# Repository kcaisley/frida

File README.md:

# FRIDA: Fast radiation imaging digitizer array

Frame-based radiation detectors with integrating front-ends are especially well-suited for applications like electron microscopy and X-ray imaging where hit-rates are high, spatial resolution should be maximized with simple pixels, and energy resolution is needed, but particles need not be individually discriminated in time, space, or spectrum. In an experimental setting, fast frame rates allow for real time in-situ observations. Potential subjects include rapid chemical processes, molecular dynamics of proteins, crystal nucleation and growth, material phase transitions, thermal conductivity, charge transfer, and mechanical strain.

This project pursues the possibility of a single-reticle array larger than 1 Mpixel with a continuous frame-rate surpassing 100,000 fps. For the conjunction of these two specifications to be met, one must have a compact and power efficient bank of column-parallel data converters, which at 10-12 bit resolution churn out data at a rate in excess of 1000 Gbps. To fit within the constraints of a chip bottom, the converter fabric must respect a restricted metric of 1 W/cm^2 while exceeding a 5 ksps/µm^2 sampling rate density. Successive-approximation ADCs are identified as the optimal choice, and various topologies and techniques will be analyzed to meet our goals.

Research question: How do we best allocate the quantity and weighting of SA bit positions, in order to yeild the highest resolution (in ENOB) for a given power, area, and power budget, and with a given amount of power supply noise?

## Block diagram of example system

## Modeling and analysis workflow

## Past designs vs current target

| Design                  | EDET DCD    | CoRDIA     | pre-Helena | Helena      |
|-------------------------|-------------|------------|------------|-------------|
| ADC resolution          | 8-bit       | 10-bit     | 8-bit      | 10-bit      |
| Conversion rate         | 10 MHz      | 2.5MHz     | 5 MHz      | 10 MHz      |
| Area of one ADC         | 100x200 μm² | 80x330 μm² | 60x800 μm² | 20x100 μm²  |
| Power of one ADC        | 1800 μW     | 30 μW      | 700 μW     | 100 μW      |
| FOM_csa (conv/sec/area) | 500 Hz/μm²  | 95 Hz/μm²  | 105 Hz/μm² | 5000 Hz/μm² |
| FOM_epc (energy/conv)   | 180 pJ      | 12 pJ      | 155 pJ     | 10 pJ       |
| FOM_ppa (power/area)    | 9.0 W/cm²   | 0.11 W/cm² | 1.45 W/cm² | 5.0 W/cm²   |
| ADC qty Mpix @ 100 KHz  | 10000       | 40000      | 20000      | 10000       |
| ADCs total pixel rate   | 100 Gpx/s   | 100 Gpx/s  | 100 Gpx/s  | 100 Gpx/s   |
| ADCs total data rate    | 800 Gb/s    | 1 Tb/s     | 800 Gb/s   | 1 Tb/s      |
| ADCs total area         | 2.0 cm²     | 10.5 cm²   | 9.6 cm²    | 0.2 cm²     |
| ADCs total power        | 35.0 W      | 1.2 W      | 14 W       | 1.0 W       |

NOTE: EDET DCD 1800 μW seems high, does it erroneously includes input amp?

# Project organization (proposal)

```
├── src
├── hdl
├── oa  (Caeleste input collateral eventually to be deleted)
├── netlists (library of generic netlists, and Verilog A models -> converted with find+replace)
├── impl
│   └── tsmc65 (1. impl netlists/oa schems/layouts/ 2. pointers to )
│   └── tsmc28
├── sim
│   └── tsmc65 (runs against impl netlists, since we have to have to include external libs)
│   └── tsmc28
├── tech
│   └── tsmc65 (EDA env start dir)
│   └── tsmc28
├── writing
```

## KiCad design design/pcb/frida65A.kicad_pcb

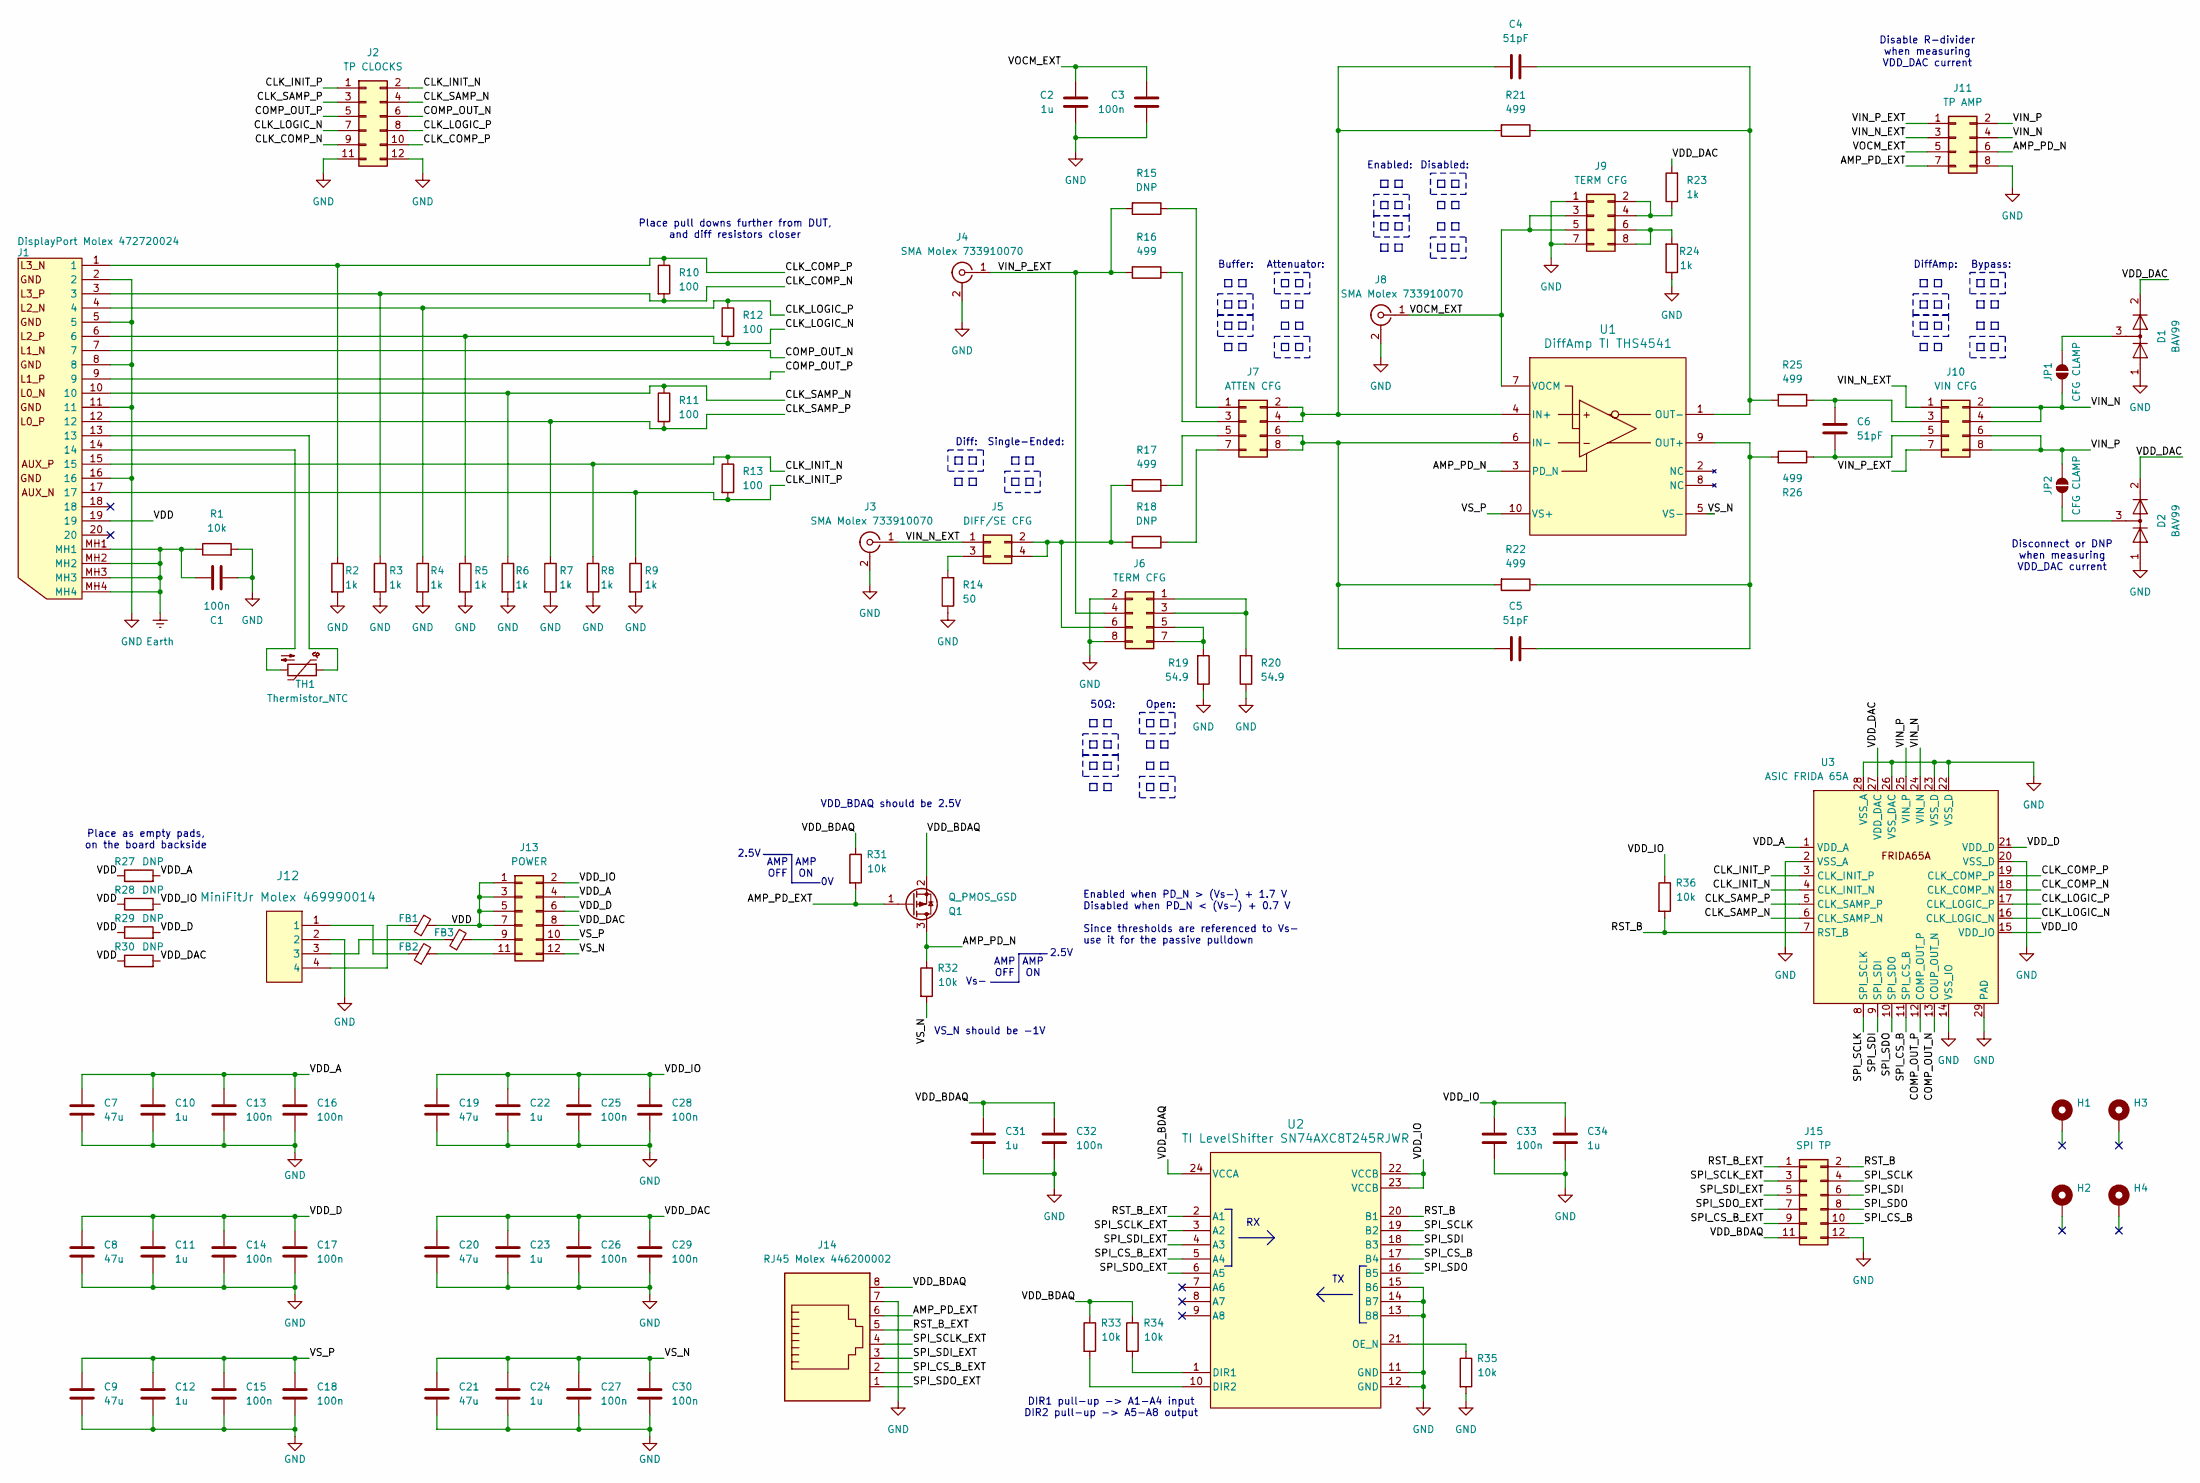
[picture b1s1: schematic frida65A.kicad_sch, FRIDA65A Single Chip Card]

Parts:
C1, C3, C13, C14, C15, C16, C17, C18, C25, C26, C27, C28, C29, C30, C32, C33: 100n; C_0402_1005Metric
C2, C10, C11, C12, C22, C23, C24, C31, C34: 1u; C_0402_1005Metric
C4, C5, C6: 51pF; C_0402_1005Metric
C7, C8, C9, C19, C20, C21: 47u; C_0402_1005Metric
D1, D2: BAV99; SOT-23
FB1, FB2, FB3: FerriteBead_Small; R_0402_1005Metric
H1, H2, H3, H4: MountingHole_Pad; MountingHole_3.2mm_M3_Pad_Via
J1: DisplayPort Molex 472720024; Molex_DisplayPort_472720024; Manufacturer_Part_Number 47272-0024; Mouser Part Number 538-47272-0024
J2: TP CLOCKS; PinHeader_2x06_P2.54mm_Vertical
J3, J4, J8: SMA Molex 733910070; Molex_SMA_733910070
J5: DIFF/SE CFG; PinHeader_2x02_P2.54mm_Vertical
J6, J9: TERM CFG; PinHeader_2x04_P2.54mm_Vertical
J7: ATTEN CFG; PinHeader_2x04_P2.54mm_Vertical
J10: VIN CFG; PinHeader_2x04_P2.54mm_Vertical
J11: TP AMP; PinHeader_2x04_P2.54mm_Vertical
J12: MiniFitJr Molex 469990014; Molex_MiniFitJr_469990014
J13: POWER; PinHeader_2x06_P2.54mm_Vertical
J14: RJ45 Molex 446200002; Molex_RJ45_446200002
J15: SPI TP; PinHeader_2x06_P2.54mm_Vertical
JP1, JP2: CFG CLAMP; SolderJumper-2_P1.3mm_Open_RoundedPad1.0x1.5mm
Q1: Q_PMOS_GSD; SOT-23
R1, R31, R32, R33, R34, R35, R36: 10k; R_0402_1005Metric
R2, R3, R4, R5, R6, R7, R8, R9, R23, R24: 1k; R_0402_1005Metric
R10, R11, R12, R13: 100; R_0402_1005Metric
R14: 50; R_0402_1005Metric
R15, R18: DNP; R_0402_1005Metric
R16, R17, R21, R22, R25, R26: 499; R_0402_1005Metric
R19, R20: 54.9; R_0402_1005Metric
R27, R28, R29, R30: DNP; R_0201_0603Metric
TH1: Thermistor_NTC; R_0402_1005Metric
U1: DiffAmp TI THS4541; TI_DiffAmp_THS4541
U2: TI LevelShifter SN74AXC8T245RJWR; TI_LevelShifter_SN74AXC8T245RJWR
U3: ASIC FRIDA 65A; FRIDA_ASIC_Pad

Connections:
/AMP_PD_EXT: J11.7, J14.6, Q1.1 (G), R31.2
/AMP_PD_N: J11.6, Q1.3 (D), R32.1, U1.3 (PD_N)
/CLK_COMP_N: J1.3, J2.9, R3.1, R10.2, U3.18 (CLK_COMP_N)
/CLK_COMP_P: J1.1, J2.10, R2.1, R10.1, U3.19 (CLK_COMP_P)
/CLK_INIT_N: J1.15, J2.2, R8.1, R13.1, U3.4 (CLK_INIT_N)
/CLK_INIT_P: J1.17, J2.1, R9.1, R13.2, U3.3 (CLK_INIT_P)
/CLK_LOGIC_N: J1.6, J2.7, R5.1, R12.2, U3.16 (CLK_LOGIC_N)
/CLK_LOGIC_P: J1.4, J2.8, R4.1, R12.1, U3.17 (CLK_LOGIC_P)
/CLK_SAMP_N: J1.10, J2.4, R6.1, R11.1, U3.6 (CLK_SAMP_N)
/CLK_SAMP_P: J1.12, J2.3, R7.1, R11.2, U3.5 (CLK_SAMP_P)
/COMP_OUT_N: J1.7, J2.6, U3.13 (COUP_OUT_N)
/COMP_OUT_P: J1.9, J2.5, U3.12 (COMP_OUT_P)
/RST_B: J15.2, R36.2, U2.20 (B1), U3.7 (RST_B)
/RST_B_EXT: J14.5, J15.1, U2.2 (A1)
/SPI_CS_B: J15.10, U2.17 (B4), U3.11 (SPI_CS_B)
/SPI_CS_B_EXT: J14.2, J15.9, U2.5 (A4)
/SPI_SCLK: J15.4, U2.19 (B2), U3.8 (SPI_SCLK)
/SPI_SCLK_EXT: J14.4, J15.3, U2.3 (A2)
/SPI_SDI: J15.6, U2.18 (B3), U3.9 (SPI_SDI)
/SPI_SDI_EXT: J14.3, J15.5, U2.4 (A3)
/SPI_SDO: J15.8, U2.16 (B5), U3.10 (SPI_SDO)
/SPI_SDO_EXT: J14.1, J15.7, U2.6 (A5)
/VDD: FB1.2, J1.19, J13.1, J13.3, J13.5, J13.7, R27.1, R28.1, R29.1, R30.1
/VDD_A: C7.1, C10.1, C13.1, C16.1, J13.4, R27.2, U3.1 (VDD_A)
/VDD_BDAQ: C31.1, C32.1, J14.8, J15.11, Q1.2 (S), R31.1, R33.1, R34.1, U2.24 (VCCA)
/VDD_D: C8.1, C11.1, C14.1, C17.1, J13.6, R29.2, U3.21 (VDD_D)
/VDD_DAC: C20.1, C23.1, C26.1, C29.1, D1.2 (A), D2.2 (A), J13.8, R23.2, R30.2, U3.27 (VDD_DAC)
/VDD_IO: C19.1, C22.1, C25.1, C28.1, C33.1, C34.1, J13.2, R28.2, R36.1, U2.22 (VCCB), U2.23 (VCCB), U3.15 (VDD_IO)
/VIN_N: J10.2, J10.4, J11.4, JP1.2 (B), U3.24 (VIN_N)
/VIN_N_EXT: J3.1 (In), J5.1, J10.1, J11.3
/VIN_P: J10.6, J10.8, J11.2, JP2.1 (A), U3.25 (VIN_P)
/VIN_P_EXT: J4.1 (In), J6.4, J10.7, J11.1, R15.2, R16.2
/VOCM_EXT: C2.1, C3.1, J8.1 (In), J9.3, J9.5, J11.5, U1.7 (VOCM)
/VS_N: C21.1, C24.1, C27.1, C30.1, J13.12, R32.2, U1.5 (VS-)
/VS_P: C9.1, C12.1, C15.1, C18.1, J13.10, U1.10 (VS+)
Earth: C1.1, J1.MH1, J1.MH2, J1.MH3, J1.MH4, R1.1
GND: C1.2, C2.2, C3.2, C7.2, C8.2, C9.2, C10.2, C11.2, C12.2, C13.2, C14.2, C15.2, C16.2, C17.2, C18.2, C19.2, C20.2, C21.2, C22.2, C23.2, C24.2, C25.2, C26.2, C27.2, C28.2, C29.2, C30.2, C31.2, C32.2, C33.2, C34.2, D1.1 (K), D2.1 (K), J1.2, J1.5, J1.8, J1.11, J1.16, J2.11, J2.12, J3.2 (Ext), J4.2 (Ext), J6.2, J6.8, J8.2 (Ext), J9.1, J9.7, J11.8, J12.2, J14.7, J15.12, R1.2, R2.2, R3.2, R4.2, R5.2, R6.2, R7.2, R8.2, R9.2, R14.1, R19.1, R20.1, R24.1, R35.2, U2.11 (GND), U2.12 (GND), U2.13 (B8), U2.14 (B7), U2.15 (B6), U3.2 (VSS_A), U3.14 (VSS_IO), U3.20 (VSS_D), U3.22 (VSS_D), U3.23 (VSS_D), U3.26 (VSS_DAC), U3.28 (VSS_A), U3.29 (PAD)
unnamed: FB1.1, J12.4
unnamed: FB2.1, J12.1
unnamed: FB3.1, J12.3
unnamed: J1.13, TH1.1
unnamed: J1.14, TH1.2
unnamed: J5.2, J5.4, J6.6, R17.2, R18.2
unnamed: J5.3, R14.2
unnamed: J6.1, J6.3, R20.2
unnamed: J6.5, J6.7, R19.2
unnamed: J7.1, R15.1
unnamed: C4.1, J7.2, J7.4, R21.2, U1.4 (IN+)
unnamed: J7.3, R16.1
unnamed: J7.5, R17.1
unnamed: C5.1, J7.6, J7.8, R22.2, U1.6 (IN-)
unnamed: J7.7, R18.1
unnamed: J9.2, J9.4, R23.1
unnamed: J9.6, J9.8, R24.2
unnamed: C6.1, J10.3, R25.1
unnamed: C6.2, J10.5, R26.1
unnamed: FB3.2, J13.9
unnamed: FB2.2, J13.11
unnamed: D1.3 (K), JP1.1 (A)
unnamed: D2.3 (K), JP2.2 (B)
unnamed: C5.2, R22.1, R26.2, U1.9 (OUT+)
unnamed: C4.2, R21.1, R25.2, U1.1 (OUT-)
unnamed: R34.2, U2.1 (DIR1)
unnamed: R33.2, U2.10 (DIR2)
unnamed: R35.1, U2.21 (OE_N)

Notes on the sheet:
2.5V
Vs-
Bypass:
DiffAmp:
Single-Ended:
Disable R-divider when measuring VDD_DAC current
AMP ON
Disconnect or DNP when measuring VDD_DAC current
Enabled when PD_N > (Vs-) + 1.7 V Disabled when PD_N < (Vs-) + 0.7 V Since thresholds are referenced to Vs- use it for the passive pulldown
Open:
Attenuator:
Place as empty pads, on the board backside
DIR1 pull-up -> A1-A4 input DIR2 pull-up -> A5-A8 output
50Ω:
Enabled:
VDD_BDAQ should be 2.5V
Diff:
Place pull downs further from DUT, and diff resistors closer
VS_N should be -1V
AMP OFF
Disabled:
Buffer:

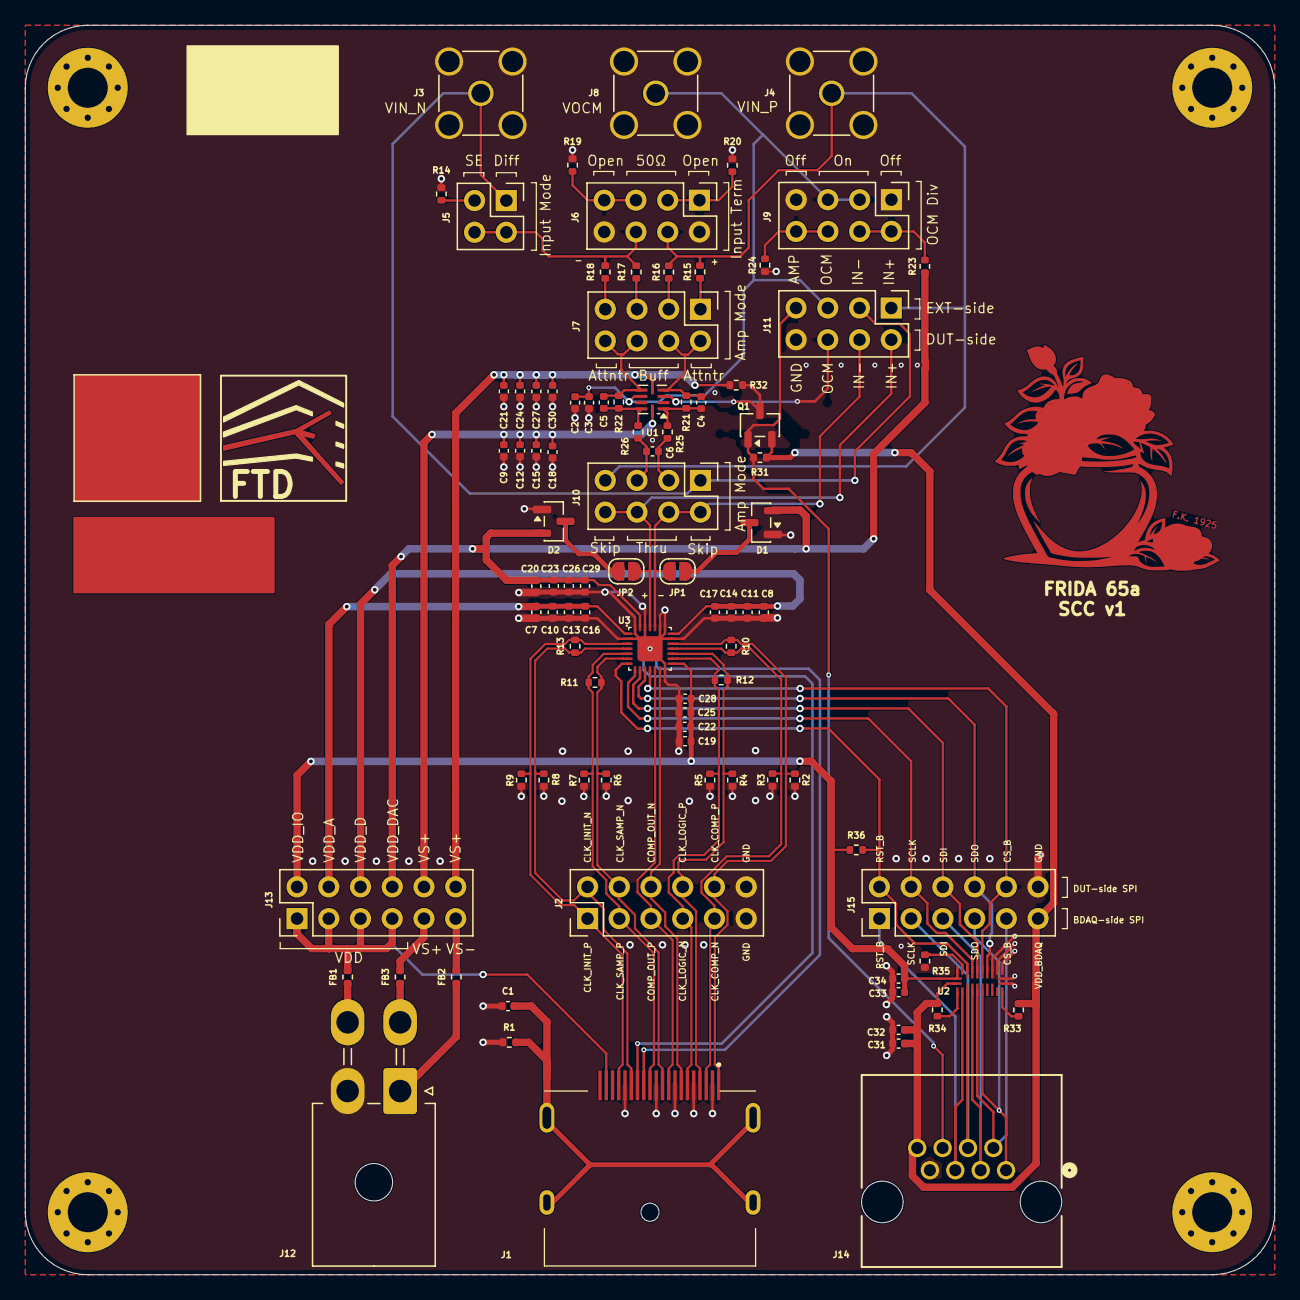
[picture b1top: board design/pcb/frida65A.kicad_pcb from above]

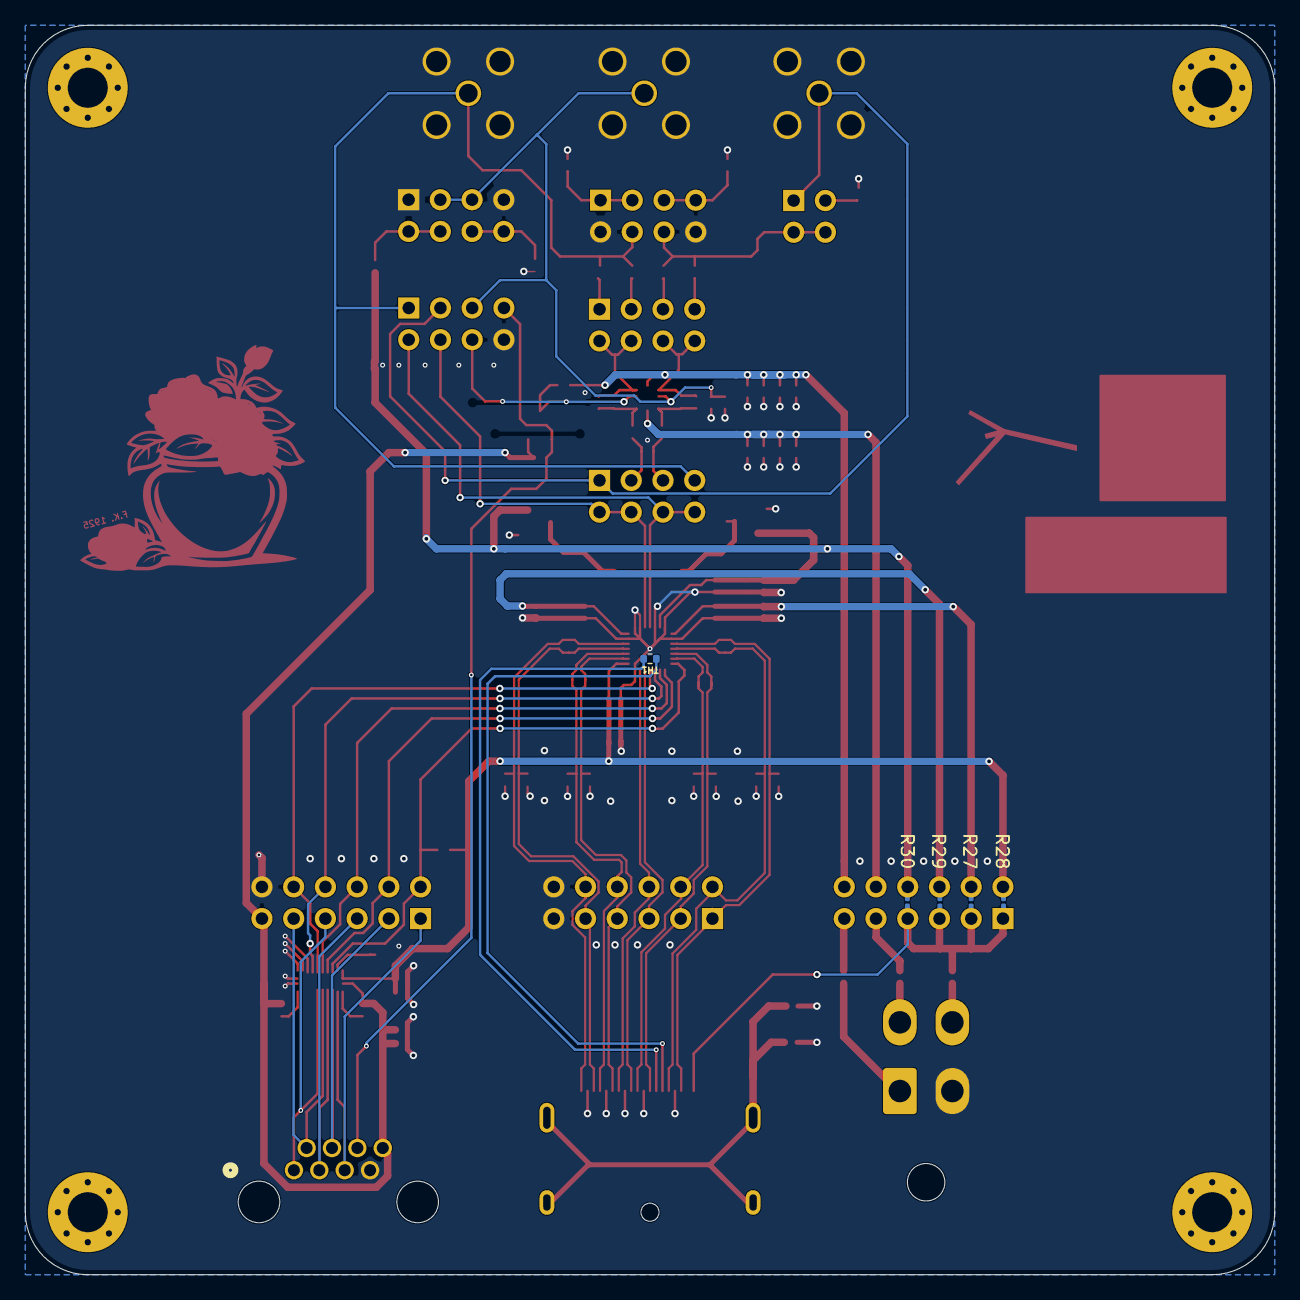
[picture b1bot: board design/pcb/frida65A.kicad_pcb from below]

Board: 4 copper layers, 100.0 x 100.0 mm, 101 parts (5 on the bottom side), 65 nets.

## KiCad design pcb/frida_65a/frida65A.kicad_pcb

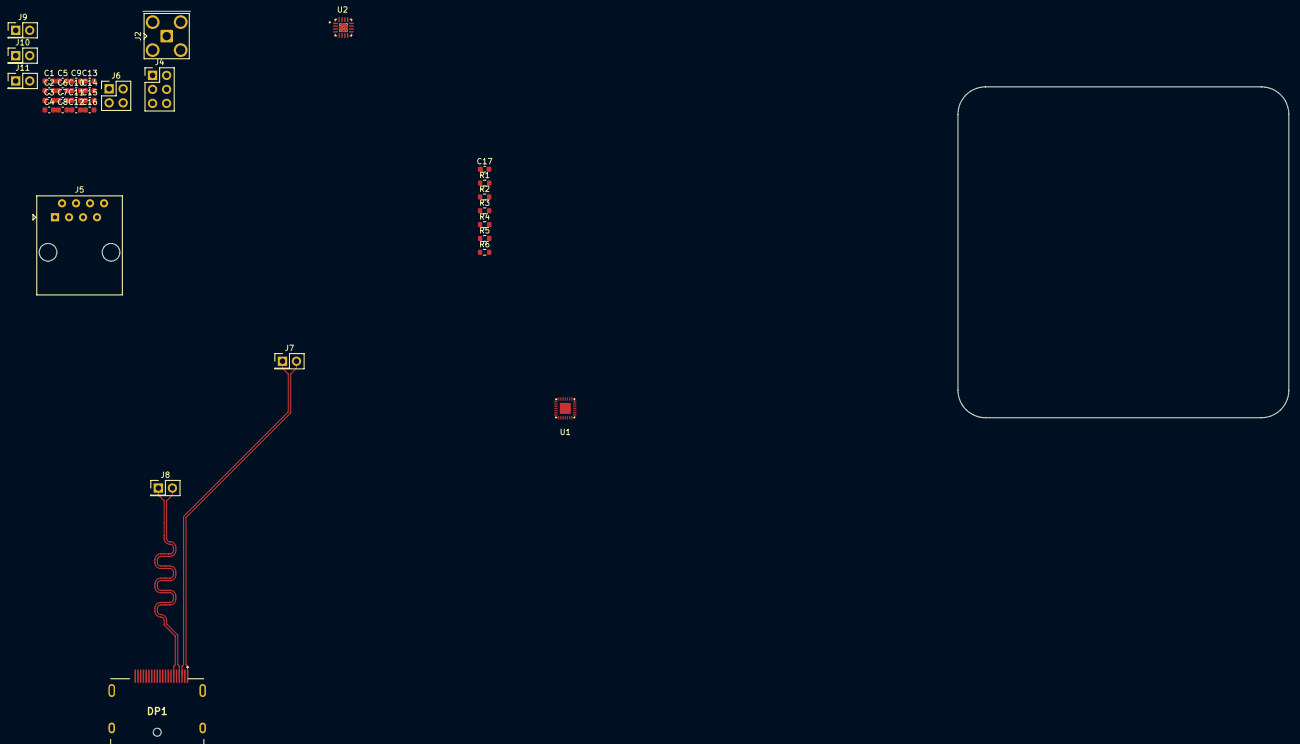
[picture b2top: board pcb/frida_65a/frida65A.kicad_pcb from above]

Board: 2 copper layers, 35 parts (0 on the bottom side), 23 nets.

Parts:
C1, C5, C9, C13: 47u; C_0603_1608Metric
C2, C6, C10, C14: 1u; C_0603_1608Metric
C3, C4, C7, C8, C11, C12, C15, C16, C17: 100n; C_0603_1608Metric
DP1: DP; DP_Molex_47272-0024
J2: CONN_IN_P; SMA_Amphenol_901-143_Horizontal
J4: TP_CFG; PinHeader_2x03_P2.54mm_Vertical
J5: CONN_CFG; RJ45_Amphenol_54602-x08_Horizontal
J6: TP_IN; PinHeader_2x02_P2.54mm_Vertical
J7: TP_INIT; PinHeader_2x01_P2.54mm_Vertical
J8: TP_SAMP; PinHeader_2x01_P2.54mm_Vertical
J9: TP_COMP; PinHeader_2x01_P2.54mm_Vertical
J10: TP_LOGIC; PinHeader_2x01_P2.54mm_Vertical
J11: TP_OUT; PinHeader_2x01_P2.54mm_Vertical
R1, R2, R3, R4, R5: 100; R_0603_1608Metric
R6: 10k; R_0603_1608Metric
U1: DUT; frida
U2: THS4520RGTT; QFN50P300X300X100-17N

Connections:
/CLK_COMP_N: DP1.7, J9.2, R3.1, U1.18 (CLK_COMP_N)
/CLK_COMP_P: DP1.9, J9.1, R3.2, U1.19 (CLK_COMP_P)
/CLK_INIT_N: DP1.1, J7.2, R1.1, U1.4 (CLK_INIT_N)
/CLK_INIT_P: DP1.3, J7.1, R1.2, U1.3 (CLK_INIT_P)
/CLK_LOGIC_N: DP1.10, J10.2, R4.1, U1.16 (CLK_LOGIC_N)
/CLK_LOGIC_P: DP1.12, J10.1, R4.2, U1.17 (CLK_LOGIC_P)
/CLK_SAMP_N: DP1.4, J8.2, R2.1, U1.6 (CLK_SAMP_N)
/CLK_SAMP_P: DP1.6, J8.1, R2.2, U1.5 (CLK_SAMP_P)
/COMP_OUT_N: DP1.15, J11.2, R5.1, U1.13 (COUP_OUT_N)
/COMP_OUT_P: DP1.17, J11.1, R5.2, U1.12 (COMP_OUT_P)
/RST_B: J4.5, J5.5, U1.7 (RST_B)
/SPI_CS_B: J4.1, J5.1, U1.11 (SPI_CS_B)
/SPI_SCLK: J4.4, J5.4, U1.8 (SPI_SCLK)
/SPI_SDI: J4.3, J5.3, U1.9 (SPI_SDI)
/SPI_SDO: J4.2, J5.2, U1.10 (SPI_SDO)
/VDD_A: C1.1, C2.1, C3.1, C4.1, U1.1 (VDD_A)
/VDD_D: C5.1, C6.1, C7.1, C8.1, U1.21 (VDD_D)
/VDD_DAC: C9.1, C10.1, C11.1, C12.1, U1.27 (VDD_DAC)
/VDD_IO: C13.1, C14.1, C15.1, C16.1, U1.15 (VDD_IO)
Earth: C17.1, DP1.MH1, DP1.MH2, DP1.MH3, DP1.MH4, R6.1
GND: C1.2, C2.2, C3.2, C4.2, C5.2, C6.2, C7.2, C8.2, C9.2, C10.2, C11.2, C12.2, C13.2, C14.2, C15.2, C16.2, C17.2, DP1.2, DP1.5, DP1.8, DP1.11, DP1.16, J2.2 (Ext), J4.6, J6.3, J6.4, R6.2, U1.2 (VSS_A), U1.14 (VSS_IO), U1.20 (VSS_D), U1.22 (VSS_D), U1.23 (VSS_D), U1.26 (VSS_DAC), U1.28 (VSS_A)
unnamed: J2.1 (In), J6.1, U1.25 (VIN_P)
unnamed: J6.2, U1.24 (VIN_N)

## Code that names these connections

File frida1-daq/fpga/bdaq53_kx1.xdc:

# ------------------------------------------------------------
# FRIDA DAQ - Constraints for BDAQ53 + Mercury KX1 (xc7k160t-1)
# ------------------------------------------------------------
#
# Pin sources:
#   System/Ethernet: bdaq53/firmware/src/bdaq53_KX1.xdc
#   DP5 pins:        Enclustra Mercury Master Pinout (Connector B)
#   RJ45 D pins:     bdaq53/firmware/src/bdaq53_KX1.xdc
#
# Signals not used by FRIDA (removed from bdaq53 reference):
#   Aurora / MGT (CLK_MGT_REF, MGT_REFCLK, MGT_RX, DP1 MGT AUX)
#   CLK200 oscillator, I2C, LEMO, PMOD, TLU (RJ45_TRIGGER/RESET)
#   mDP_ML (mini DisplayPort), GPIO_RESET, GPIO_SENSE, NTC_MUX
#   USER_BUTTON, derived clocks (I2C_CLK, SPI_CLK)

# ===== Clocks =====
create_clock -period 10.000 -name CLK_SYS -add [get_ports FCLK_IN]
create_clock -period 8.000 -name CLK_RGMII_RX -add [get_ports rgmii_rxc]

set_clock_groups -asynchronous \
    -group {BUS_CLK_PLL} \
    -group {CLK125PLLTX CLK125PLLTX90} \
    -group CLK_RGMII_RX \
    -group {SEQ_CLK_PLL}  ;# seq_gen config regs are stable before sequencer starts

# ===== SiTCP timing =====
set_max_delay -datapath_only -from [get_clocks CLK125PLLTX] -to [get_ports {rgmii_txd[*]}] 4.000
set_max_delay -datapath_only -from [get_clocks CLK125PLLTX] -to [get_ports rgmii_tx_ctl] 4.000
set_max_delay -datapath_only -from [get_clocks CLK125PLLTX90] -to [get_ports rgmii_txc] 4.000
set_property ASYNC_REG true [get_cells sitcp/SiTCP/GMII/GMII_TXCNT/irMacPauseExe_0]
set_property ASYNC_REG true [get_cells sitcp/SiTCP/GMII/GMII_TXCNT/irMacPauseExe_1]

# ===== System clock (100 MHz) =====
set_property PACKAGE_PIN AA3 [get_ports FCLK_IN]
set_property IOSTANDARD LVCMOS15 [get_ports FCLK_IN]

# ===== Reset button =====
set_property PACKAGE_PIN C18 [get_ports RESET_BUTTON]
set_property IOSTANDARD LVCMOS25 [get_ports RESET_BUTTON]
set_property PULLUP true [get_ports RESET_BUTTON]

# ===== User button (SW_USER_B, active low) =====
set_property PACKAGE_PIN AF22 [get_ports USER_BUTTON]
set_property IOSTANDARD LVCMOS25 [get_ports USER_BUTTON]
set_property PULLUP true [get_ports USER_BUTTON]

# ===== LEDs =====
# LED 0..3: onboard KX1 module LEDs (Bank 15, LVCMOS25)
set_property PACKAGE_PIN M17 [get_ports {LED[0]}]
set_property PACKAGE_PIN L18 [get_ports {LED[1]}]
set_property PACKAGE_PIN L17 [get_ports {LED[2]}]
set_property PACKAGE_PIN K18 [get_ports {LED[3]}]
# LED 4..7: BDAQ53 base board LEDs (LVCMOS25)
set_property PACKAGE_PIN P26 [get_ports {LED[4]}]
set_property PACKAGE_PIN M25 [get_ports {LED[5]}]
set_property PACKAGE_PIN L25 [get_ports {LED[6]}]
set_property PACKAGE_PIN P23 [get_ports {LED[7]}]
set_property IOSTANDARD LVCMOS25 [get_ports {LED[*]}]
set_property SLEW SLOW [get_ports LED*]

# ===== EEPROM (SPI for SiTCP) =====
set_property PACKAGE_PIN G14 [get_ports EEPROM_CS]
set_property PACKAGE_PIN H11 [get_ports EEPROM_SK]
set_property PACKAGE_PIN D8 [get_ports EEPROM_DI]
set_property PACKAGE_PIN A8 [get_ports EEPROM_DO]
set_property IOSTANDARD LVCMOS33 [get_ports EEPROM_*]

# ===== Ethernet (RGMII) =====
set_property SLEW FAST [get_ports mdio_phy_mdc]
set_property IOSTANDARD LVCMOS25 [get_ports mdio_phy_mdc]
set_property PACKAGE_PIN N16 [get_ports mdio_phy_mdc]

set_property SLEW FAST [get_ports mdio_phy_mdio]
set_property IOSTANDARD LVCMOS25 [get_ports mdio_phy_mdio]
set_property PACKAGE_PIN U16 [get_ports mdio_phy_mdio]

set_property SLEW FAST [get_ports phy_rst_n]
set_property IOSTANDARD LVCMOS25 [get_ports phy_rst_n]
set_property PACKAGE_PIN M20 [get_ports phy_rst_n]

set_property IOSTANDARD LVCMOS25 [get_ports rgmii_rxc]
set_property PACKAGE_PIN R21 [get_ports rgmii_rxc]
set_property IOSTANDARD LVCMOS25 [get_ports rgmii_rx_ctl]
set_property PACKAGE_PIN P21 [get_ports rgmii_rx_ctl]
set_property IOSTANDARD LVCMOS25 [get_ports {rgmii_rxd[0]}]
set_property PACKAGE_PIN P16 [get_ports {rgmii_rxd[0]}]
set_property IOSTANDARD LVCMOS25 [get_ports {rgmii_rxd[1]}]
set_property PACKAGE_PIN N17 [get_ports {rgmii_rxd[1]}]
set_property IOSTANDARD LVCMOS25 [get_ports {rgmii_rxd[2]}]
set_property PACKAGE_PIN R16 [get_ports {rgmii_rxd[2]}]
set_property IOSTANDARD LVCMOS25 [get_ports {rgmii_rxd[3]}]
set_property PACKAGE_PIN R17 [get_ports {rgmii_rxd[3]}]

set_property SLEW FAST [get_ports rgmii_txc]
set_property IOSTANDARD LVCMOS25 [get_ports rgmii_txc]
set_property PACKAGE_PIN R18 [get_ports rgmii_txc]
set_property SLEW FAST [get_ports rgmii_tx_ctl]
set_property IOSTANDARD LVCMOS25 [get_ports rgmii_tx_ctl]
set_property PACKAGE_PIN P18 [get_ports rgmii_tx_ctl]
set_property SLEW FAST [get_ports {rgmii_txd[0]}]
set_property IOSTANDARD LVCMOS25 [get_ports {rgmii_txd[0]}]
set_property PACKAGE_PIN N18 [get_ports {rgmii_txd[0]}]
set_property SLEW FAST [get_ports {rgmii_txd[1]}]
set_property IOSTANDARD LVCMOS25 [get_ports {rgmii_txd[1]}]
set_property PACKAGE_PIN M19 [get_ports {rgmii_txd[1]}]
set_property SLEW FAST [get_ports {rgmii_txd[2]}]
set_property IOSTANDARD LVCMOS25 [get_ports {rgmii_txd[2]}]
set_property PACKAGE_PIN U17 [get_ports {rgmii_txd[2]}]
set_property SLEW FAST [get_ports {rgmii_txd[3]}]
set_property IOSTANDARD LVCMOS25 [get_ports {rgmii_txd[3]}]
set_property PACKAGE_PIN T17 [get_ports {rgmii_txd[3]}]

# ===== FRIDA chip: DP5 (DP_ML, SelectIOs) =====
# 4 LVDS pairs (sequencer clocks) + AUX (comp_out)
# Pin mapping from Enclustra Mercury Master Pinout, Connector B
set_property PACKAGE_PIN K16 [get_ports CLK_INIT_P]
set_property PACKAGE_PIN K17 [get_ports CLK_INIT_N]
set_property PACKAGE_PIN L19 [get_ports CLK_SAMP_P]
set_property PACKAGE_PIN L20 [get_ports CLK_SAMP_N]
set_property PACKAGE_PIN H17 [get_ports CLK_COMP_P]
set_property PACKAGE_PIN H18 [get_ports CLK_COMP_N]
set_property PACKAGE_PIN G19 [get_ports CLK_LOGIC_P]
set_property PACKAGE_PIN F20 [get_ports CLK_LOGIC_N]
set_property IOSTANDARD LVDS_25 [get_ports CLK_*_P]
set_property IOSTANDARD LVDS_25 [get_ports CLK_*_N]
set_property PACKAGE_PIN H19 [get_ports COMP_OUT_P]
set_property PACKAGE_PIN G20 [get_ports COMP_OUT_N]
set_property IOSTANDARD LVDS_25 [get_ports COMP_OUT_*]

# ===== FRIDA chip: RJ45 port D (single-ended) =====
# 4 diff pairs = 8 pins, used as single-ended for SPI + GPIO
# Pin mapping from bdaq53_KX1.xdc (RJ45 D / IOD block)
# Signal-to-pin assignment from SCC schematic (J12 RJ45 pinout):
#   Pin 1: SPI_CS_B  → A18  (DATA_B4_P)
#   Pin 2: SPI_SDO   → A19  (DATA_B4_N)
#   Pin 3: SPI_SDI   → F17  (DATA_B2_N)
#   Pin 4: SPI_SCLK  → E15  (DATA_B3_P)
#   Pin 5: RST_B     → E16  (DATA_B3_N)
#   Pin 6: AMPEN_B   → E17  (DATA_B2_P)
#   Pin 7: VSS_LS → G15  (DATA_B1_P, level shifter VCCB low ref)
#   Pin 8: VDD_LS → F15  (DATA_B1_N, level shifter VCCB high ref)
set_property PACKAGE_PIN G15 [get_ports VSS_LS]
set_property PACKAGE_PIN F15 [get_ports VDD_LS]
set_property IOSTANDARD LVCMOS25 [get_ports V*_LS]
set_property PACKAGE_PIN A18 [get_ports SPI_CS_B]
set_property PACKAGE_PIN A19 [get_ports SPI_SDO]
set_property PACKAGE_PIN F17 [get_ports SPI_SDI]
set_property PACKAGE_PIN E15 [get_ports SPI_SCLK]
set_property PACKAGE_PIN E16 [get_ports RST_B]
set_property PACKAGE_PIN E17 [get_ports AMPEN_B]
set_property IOSTANDARD LVCMOS25 [get_ports SPI_*]
set_property IOSTANDARD LVCMOS25 [get_ports RST_B]
set_property IOSTANDARD LVCMOS25 [get_ports AMPEN_B]

# ===== SPI configuration flash =====
set_property CONFIG_MODE SPIx4 [current_design]
set_property BITSTREAM.GENERAL.COMPRESS TRUE [current_design]
set_property BITSTREAM.CONFIG.CONFIGRATE 33 [current_design]
